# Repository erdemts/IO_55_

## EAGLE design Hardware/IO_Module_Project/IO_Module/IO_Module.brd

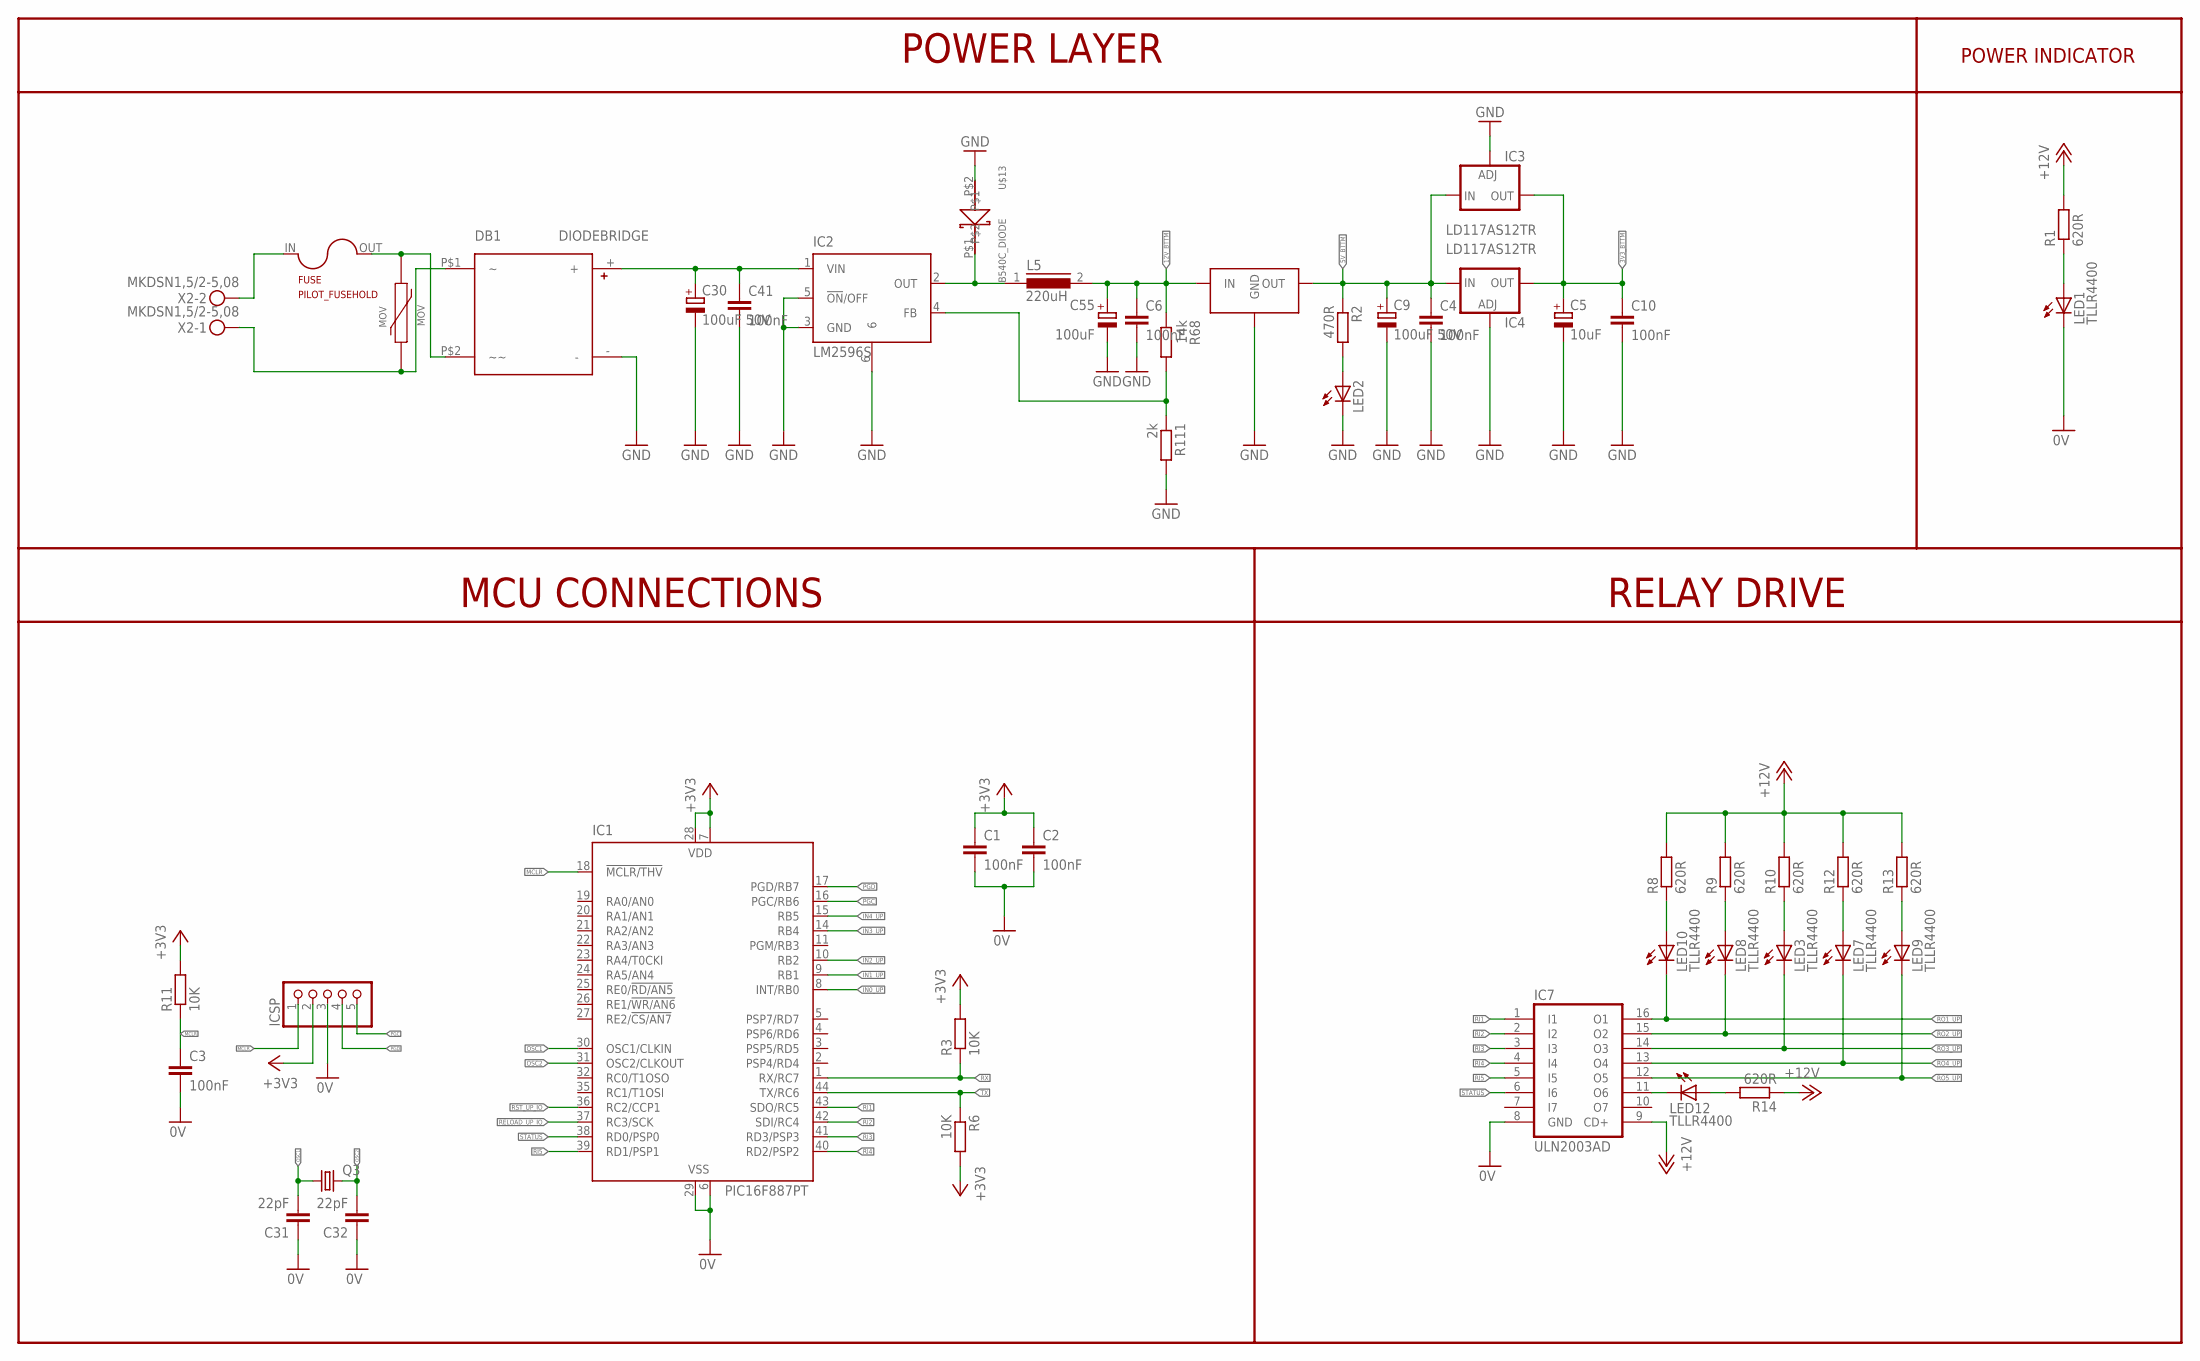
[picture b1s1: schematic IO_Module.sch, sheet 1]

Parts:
C1, C2, C3: 100nF; C0603K
C4, C6, C10, C41: 100nF; C0603
C5: 10uF; 153CLV-0505
C9, C30: 100uF 50V; 153CLV-0810
C31, C32: 22pF; C0805
C55: 100uF; 153CLV-0605
DB1: DIODEBRIDGE; SDIP
FUSE: PILOT_FUSEHOLD; RTM_FUSEHOLD
IC1: PIC16F887PT; TQFP44
IC2: LM2596S; TO263-5
IC3, IC4: LD117AS12TR; SOT223
IC7: ULN2003AD; SO16
ICSP: PINHD-1X5; 1X05
L5: 220uH; DR125
LED1, LED3, LED7, LED8, LED9, LED10, LED12: TLLR4400; LED3MM
LED2: LEDCHIPLED_0805; CHIPLED_0805
MOV: MOV-10D201K
Q3: CRYSTALHC49UP; HC49UP
R1, R8, R9, R10, R12, R13, R14: 620R; R0805
R2: 470R; R0805
R3, R6, R11: 10K; R0805
R68: 14k; M0805
R111: 2k; M0805
U$6: L7805CD2T-TR; VREG-7805-DPAK2
U$13: B540C_DIODE; SMC
X2: MKDSN1,5/2-5,08

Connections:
0V: C1.2, C2.2, C3.2, C31.1, C32.1, IC1.6 (VSS), IC1.29 (VSS), IC7.8 (GND), ICSP.3, LED1.K (C); also elsewhere on the board
3V3_BTTM: C5.+, C10.1, IC3.4 (OUT), IC4.4 (OUT); also elsewhere on the board
5V_BTTM: C4.1, C9.+, IC3.3 (IN), IC4.3 (IN), R2.1, U$6.VOUT (OUT)
12V_BTTM: C6.1, C55.+, L5.2, R68.1, U$6.VIN (IN); also elsewhere on the board
36V: C30.+, C41.1, DB1.+, IC2.1 (VIN)
+3V3: C1.1, C2.1, IC1.7 (VDD), IC1.28 (VDD), ICSP.2, R3.2, R6.2, R11.2; also elsewhere on the board
+12V: IC7.9 (CD+), R1.2, R8.2, R9.2, R10.2, R12.2, R13.2, R14.1; also elsewhere on the board
GND: C4.2, C5.-, C6.2, C9.-, C10.2, C30.-, C41.2, C55.-, DB1.-, IC2.3 (GND), IC2.5 (!ON!/OFF), IC2.6, IC3.1 (ADJ), IC4.1 (ADJ), LED2.C, R111.2, U$6.GND, U$13.P$2; also elsewhere on the board
IN0_UP: IC1.8 (INT/RB0); also elsewhere on the board
IN1_UP: IC1.9 (RB1); also elsewhere on the board
IN2_UP: IC1.10 (RB2); also elsewhere on the board
IN3_UP: IC1.14 (RB4); also elsewhere on the board
IN4_UP: IC1.15 (RB5); also elsewhere on the board
MCLR: C3.1, IC1.18 (!MCLR/THV), ICSP.1, R11.1
unnamed: LED2.A, R2.2
unnamed: DB1.P$2 (~~), FUSE.OUT, MOV.2
unnamed: DB1.P$1, MOV.1, X2.1
unnamed: FUSE.IN, X2.2
unnamed: LED1.A, R1.1
unnamed: IC7.11 (O6), LED12.K (C)
unnamed: LED10.A, R8.1
unnamed: LED8.A, R9.1
unnamed: LED3.A, R10.1
unnamed: LED7.A, R12.1
unnamed: LED9.A, R13.1
unnamed: LED12.A, R14.2
unnamed: IC2.2 (OUT), L5.1, U$13.P$1
unnamed: IC2.4 (FB), R68.2, R111.1
OSC1: C31.2, IC1.30 (OSC1/CLKIN), Q3.1
OSC2: C32.2, IC1.31 (OSC2/CLKOUT), Q3.2
PGC: IC1.16 (PGC/RB6), ICSP.5
PGD: IC1.17 (PGD/RB7), ICSP.4
RELOAD_UP_IO: IC1.37 (RC3/SCK); also elsewhere on the board
RI1: IC1.43 (SDO/RC5), IC7.1 (I1)
RI2: IC1.42 (SDI/RC4), IC7.2 (I2)
RI3: IC1.41 (RD3/PSP3), IC7.3 (I3)
RI4: IC1.40 (RD2/PSP2), IC7.4 (I4)
RI5: IC1.39 (RD1/PSP1), IC7.5 (I5)
RO1_UP: IC7.16 (O1), LED10.K (C); also elsewhere on the board
RO2_UP: IC7.15 (O2), LED8.K (C); also elsewhere on the board
RO3_UP: IC7.14 (O3), LED3.K (C); also elsewhere on the board
RO4_UP: IC7.13 (O4), LED7.K (C); also elsewhere on the board
RO5_UP: IC7.12 (O5), LED9.K (C); also elsewhere on the board
RST_UP_IO: IC1.36 (RC2/CCP1); also elsewhere on the board
RX: IC1.1 (RX/RC7), R3.1; also elsewhere on the board
STATUS: IC1.38 (RD0/PSP0), IC7.6 (I6)
TX: IC1.44 (TX/RC6), R6.1; also elsewhere on the board

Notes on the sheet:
POWER LAYER
MCU CONNECTIONS
RELAY DRIVE
POWER INDICATOR

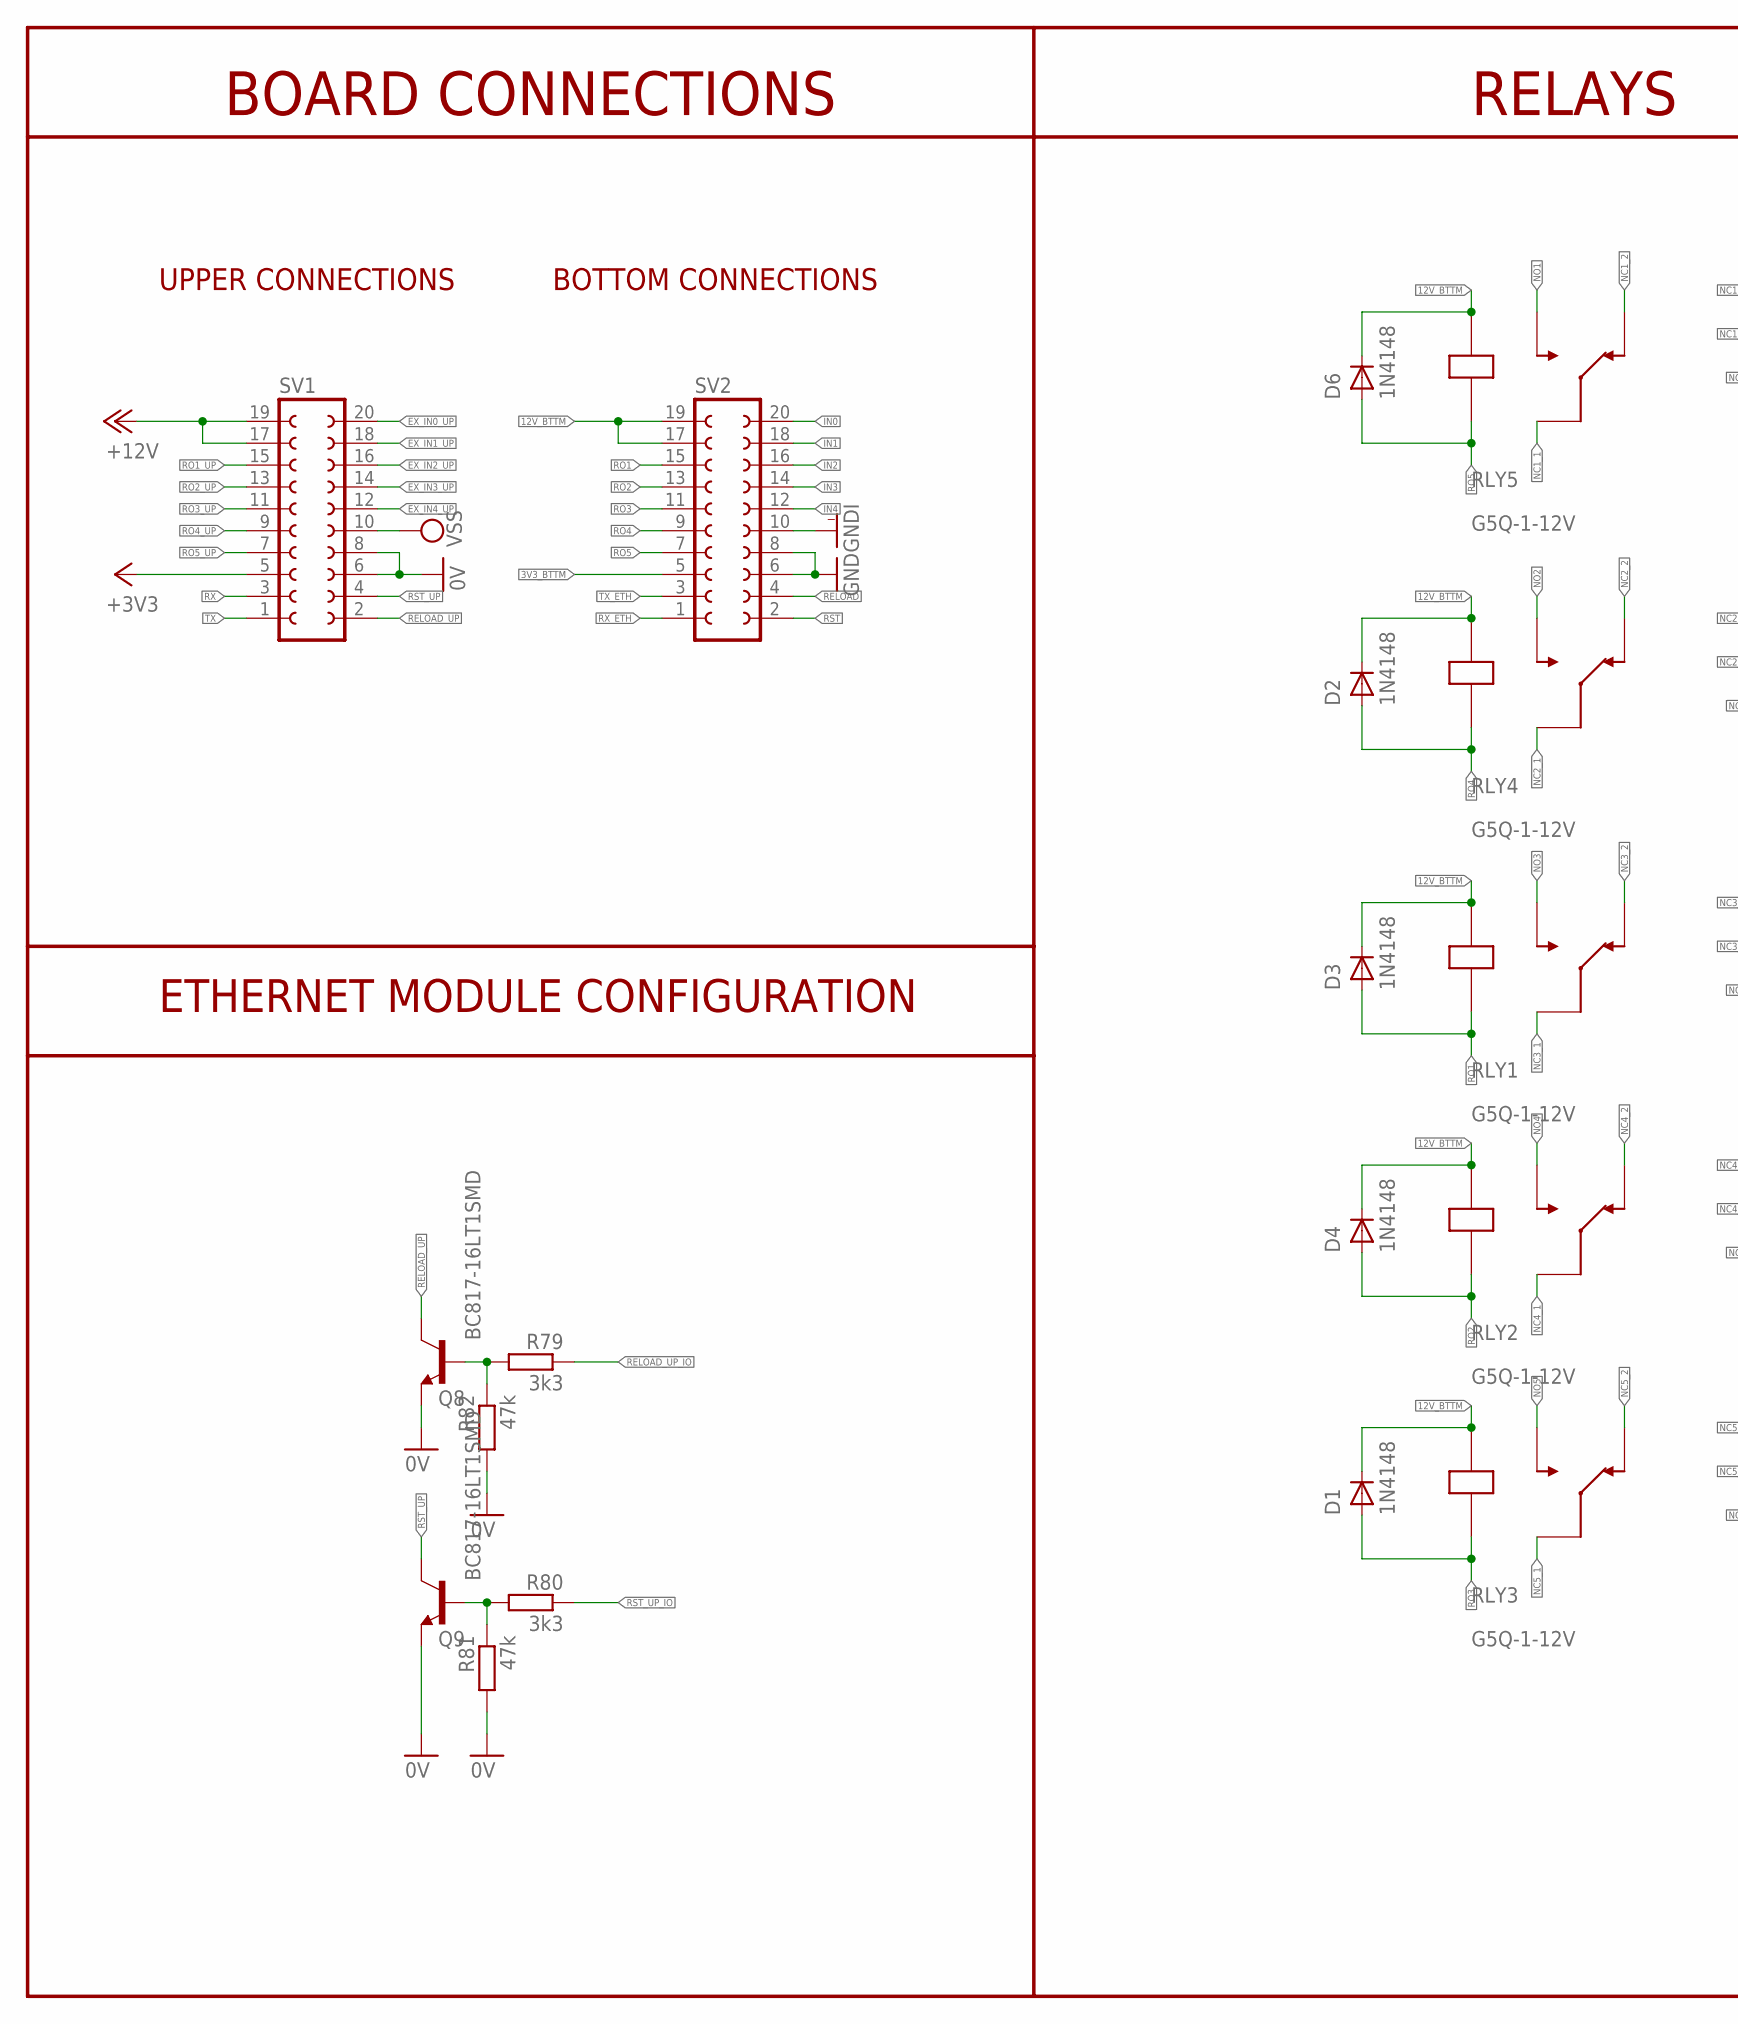
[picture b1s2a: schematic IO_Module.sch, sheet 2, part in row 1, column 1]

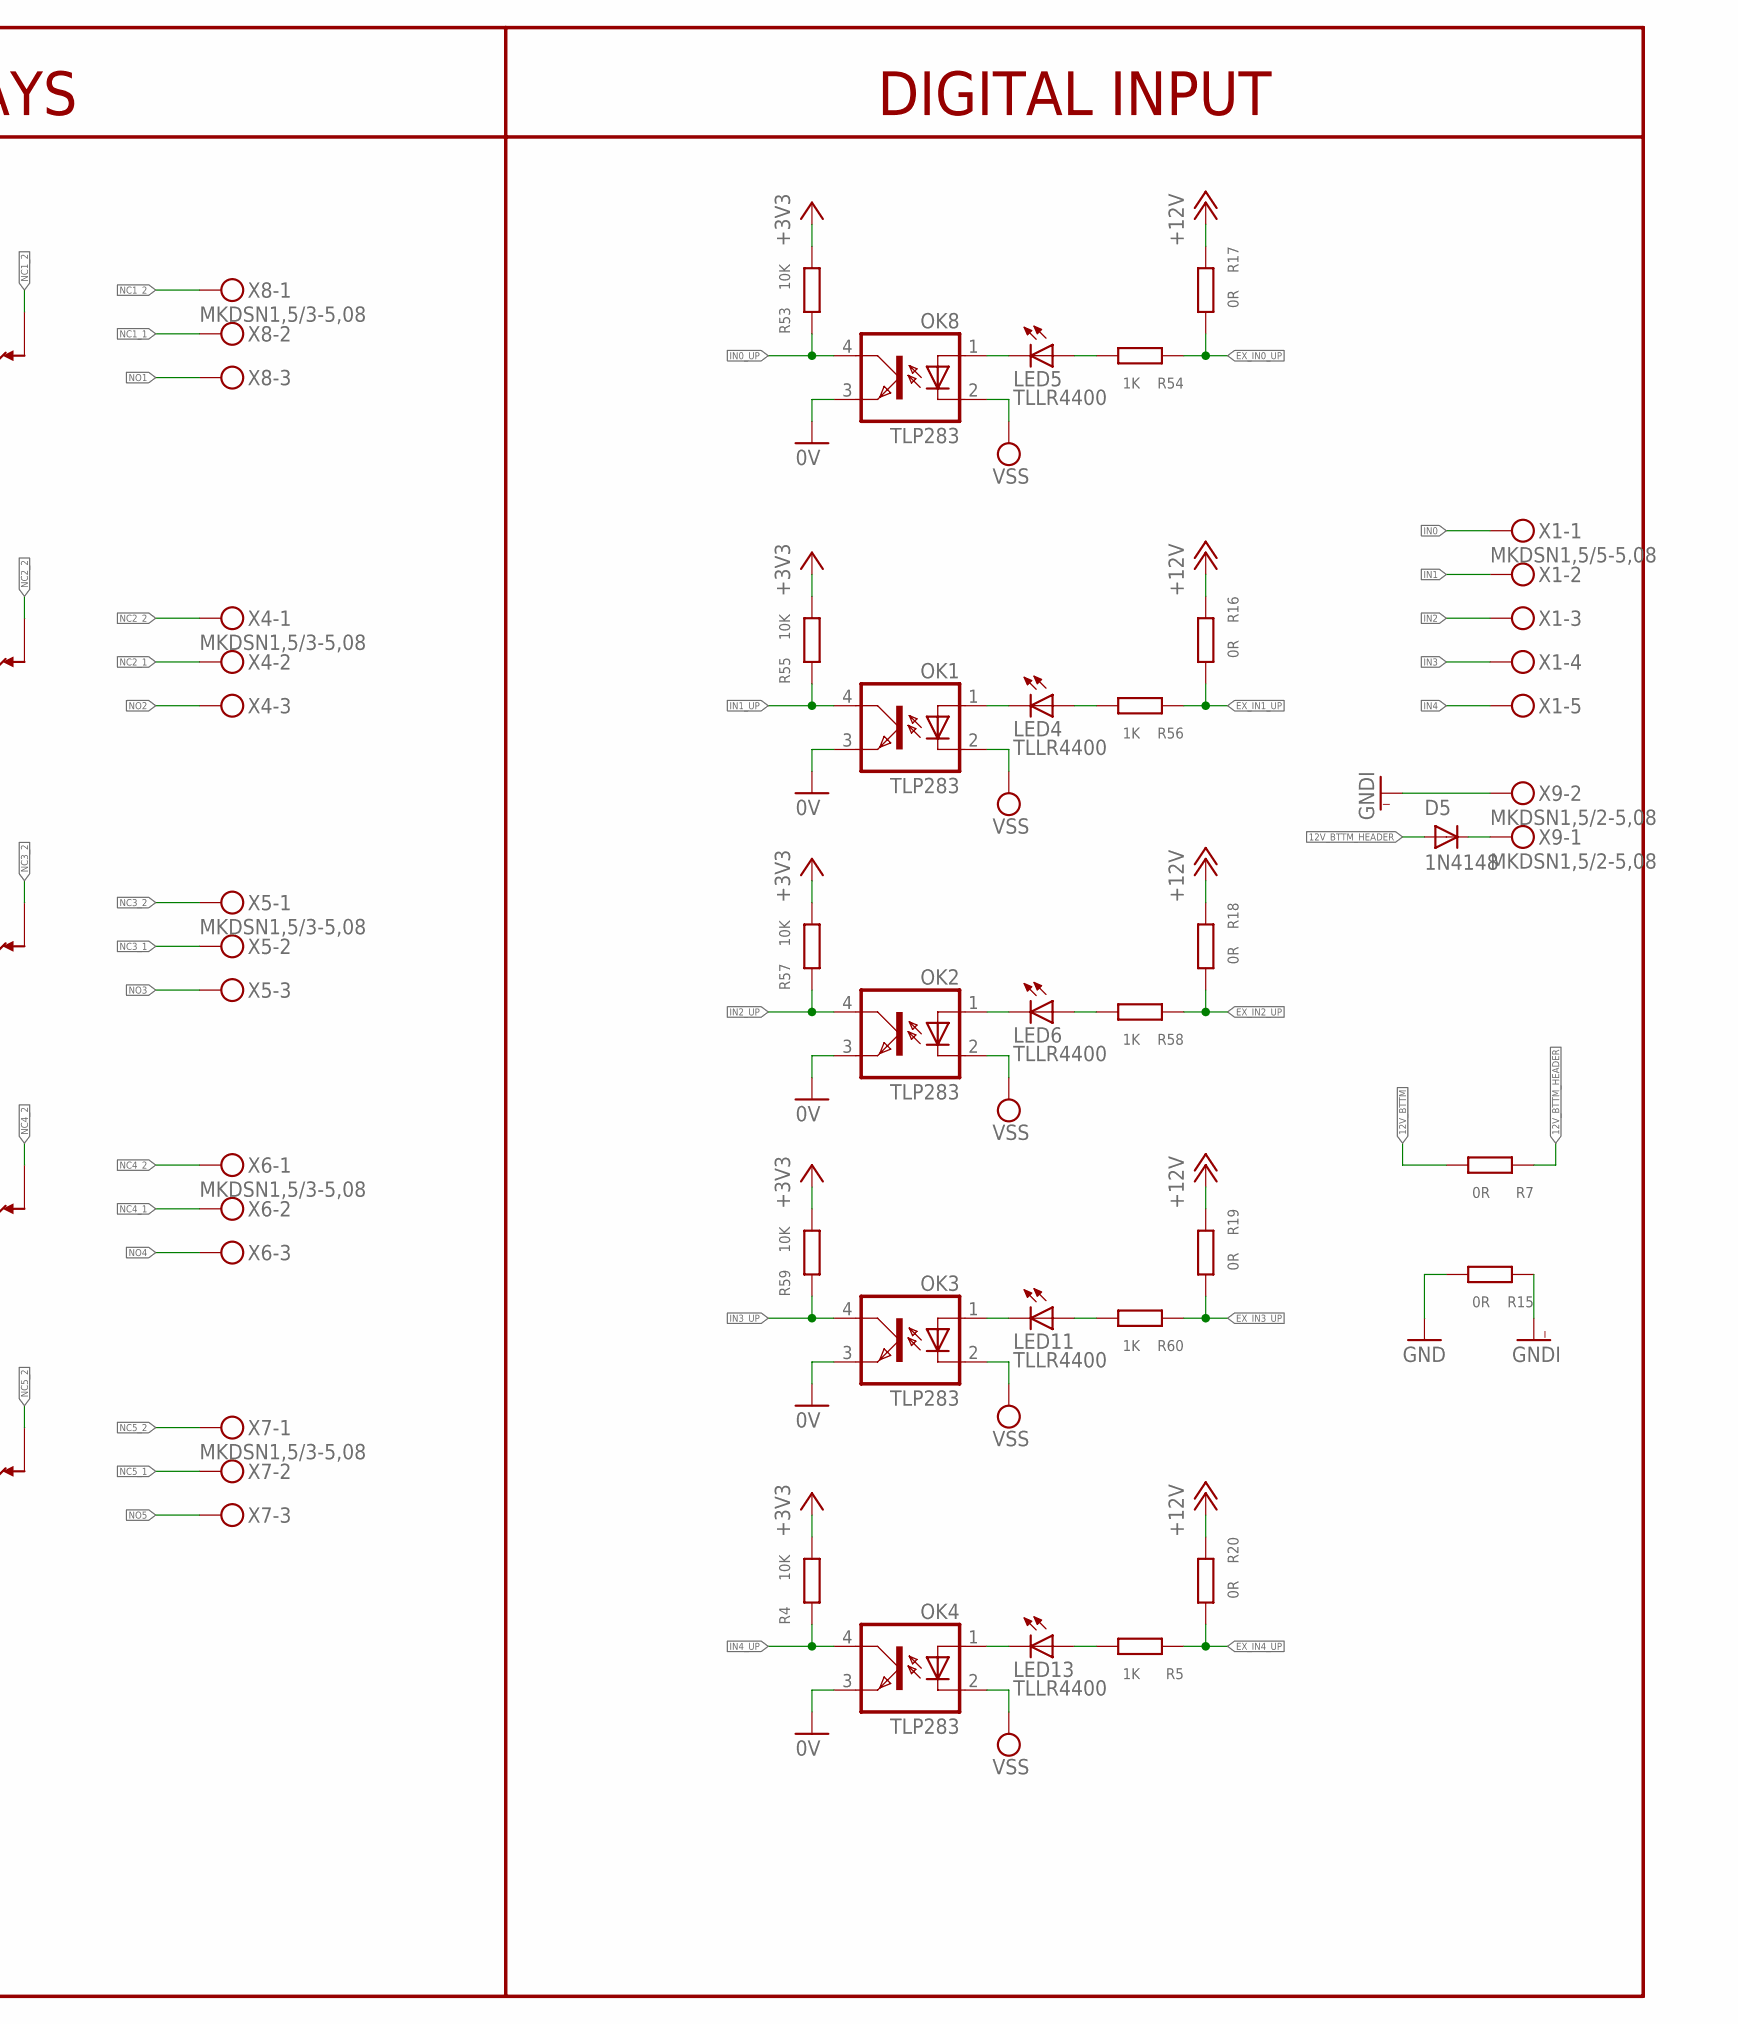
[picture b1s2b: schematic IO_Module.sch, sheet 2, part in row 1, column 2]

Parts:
D1, D2, D3, D4, D5, D6: 1N4148; SMA-DO214AC
LED4, LED5, LED6, LED11, LED13: TLLR4400; LED3MM
OK1, OK2, OK3, OK4, OK8: TLP283; MINI-FLAT-4
Q8, Q9: BC817-16LT1SMD; SOT23-BEC
R4, R53, R55, R57, R59: 10K; M0805
R5, R54, R56, R58, R60: 1K; M0805
R7, R15, R16, R17, R18, R19, R20: 0R; M0805
R79, R80: 3k3; R0805
R81, R82: 47k; R0805
RLY1, RLY2, RLY3, RLY4, RLY5: JW1FSN-DC12V; G5Q-1-12V
SV1, SV2: FE10-2
X1: MKDSN1,5/5-5,08
X4, X5, X6, X7, X8: MKDSN1,5/3-5,08
X9: MKDSN1,5/2-5,08

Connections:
0V: OK1.3 (EMIT), OK2.3 (EMIT), OK3.3 (EMIT), OK4.3 (EMIT), OK8.3 (EMIT), Q8.E, Q9.E, R81.2, R82.2, SV1.6, SV1.8; also elsewhere on the board
3V3_BTTM: SV2.5; also elsewhere on the board
12V_BTTM: D1.K (C), D2.K (C), D3.K (C), D4.K (C), D6.K (C), R7.2, RLY1.1, RLY2.1, RLY3.1, RLY4.1, RLY5.1, SV2.17, SV2.19; also elsewhere on the board
12V_BTTM_HEADER: D5.A, R7.1
+3V3: R4.2, R53.2, R55.2, R57.2, R59.2, SV1.5; also elsewhere on the board
+12V: R16.1, R17.1, R18.1, R19.1, R20.1, SV1.17, SV1.19; also elsewhere on the board
EX_IN0_UP: R17.2, R54.1, SV1.20
EX_IN1_UP: R16.2, R56.1, SV1.18
EX_IN2_UP: R18.2, R58.1, SV1.16
EX_IN3_UP: R19.2, R60.1, SV1.14
EX_IN4_UP: R5.1, R20.2, SV1.12
GND: R15.2, SV2.6, SV2.8; also elsewhere on the board
GNDI: R15.1, SV2.10, X9.2
IN0: SV2.20, X1.1
IN0_UP: OK8.4 (COL), R53.1; also elsewhere on the board
IN1: SV2.18, X1.2
IN1_UP: OK1.4 (COL), R55.1; also elsewhere on the board
IN2: SV2.16, X1.3
IN2_UP: OK2.4 (COL), R57.1; also elsewhere on the board
IN3: SV2.14, X1.4
IN3_UP: OK3.4 (COL), R59.1; also elsewhere on the board
IN4: SV2.12, X1.5
IN4_UP: OK4.4 (COL), R4.1; also elsewhere on the board
unnamed: LED13.K (C), OK4.1 (A)
unnamed: LED13.A, R5.2
unnamed: D5.K (C), X9.1
unnamed: LED5.K (C), OK8.1 (A)
unnamed: LED5.A, R54.2
unnamed: LED4.K (C), OK1.1 (A)
unnamed: LED4.A, R56.2
unnamed: LED6.K (C), OK2.1 (A)
unnamed: LED6.A, R58.2
unnamed: LED11.K (C), OK3.1 (A)
unnamed: LED11.A, R60.2
NC1_1: RLY5.3, X8.2
NC1_2: RLY5.4, X8.1
NC2_1: RLY4.3, X4.2
NC2_2: RLY4.4, X4.1
NC3_1: RLY1.3, X5.2
NC3_2: RLY1.4, X5.1
NC4_1: RLY2.3, X6.2
NC4_2: RLY2.4, X6.1
NC5_1: RLY3.3, X7.2
NC5_2: RLY3.4, X7.1
NO1: RLY5.5, X8.3
NO2: RLY4.5, X4.3
NO3: RLY1.5, X5.3
NO4: RLY2.5, X6.3
NO5: RLY3.5, X7.3
RELOAD: SV2.4; also elsewhere on the board
RELOAD_UP: Q8.C, SV1.2
RELOAD_UP_IO: R79.1; also elsewhere on the board
RO1: D3.A, RLY1.2, SV2.15
RO1_UP: SV1.15; also elsewhere on the board
RO2: D4.A, RLY2.2, SV2.13
RO2_UP: SV1.13; also elsewhere on the board
RO3: D1.A, RLY3.2, SV2.11
RO3_UP: SV1.11; also elsewhere on the board
RO4: D2.A, RLY4.2, SV2.9
RO4_UP: SV1.9; also elsewhere on the board
RO5: D6.A, RLY5.2, SV2.7
RO5_UP: SV1.7; also elsewhere on the board
RST: SV2.2; also elsewhere on the board
RST_UP: Q9.C, SV1.4
RST_UP_IO: R80.1; also elsewhere on the board
RX: SV1.3; also elsewhere on the board
RX_ETH: SV2.1; also elsewhere on the board
TX: SV1.1; also elsewhere on the board
TXD2: Q8.B, R79.2, R82.1
TXD3: Q9.B, R80.2, R81.1
TX_ETH: SV2.3; also elsewhere on the board
VSS: OK1.2 (C), OK2.2 (C), OK3.2 (C), OK4.2 (C), OK8.2 (C), SV1.10

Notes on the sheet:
UPPER CONNECTIONS
BOTTOM CONNECTIONS
ETHERNET MODULE CONFIGURATION
BOARD CONNECTIONS
RELAYS
DIGITAL INPUT

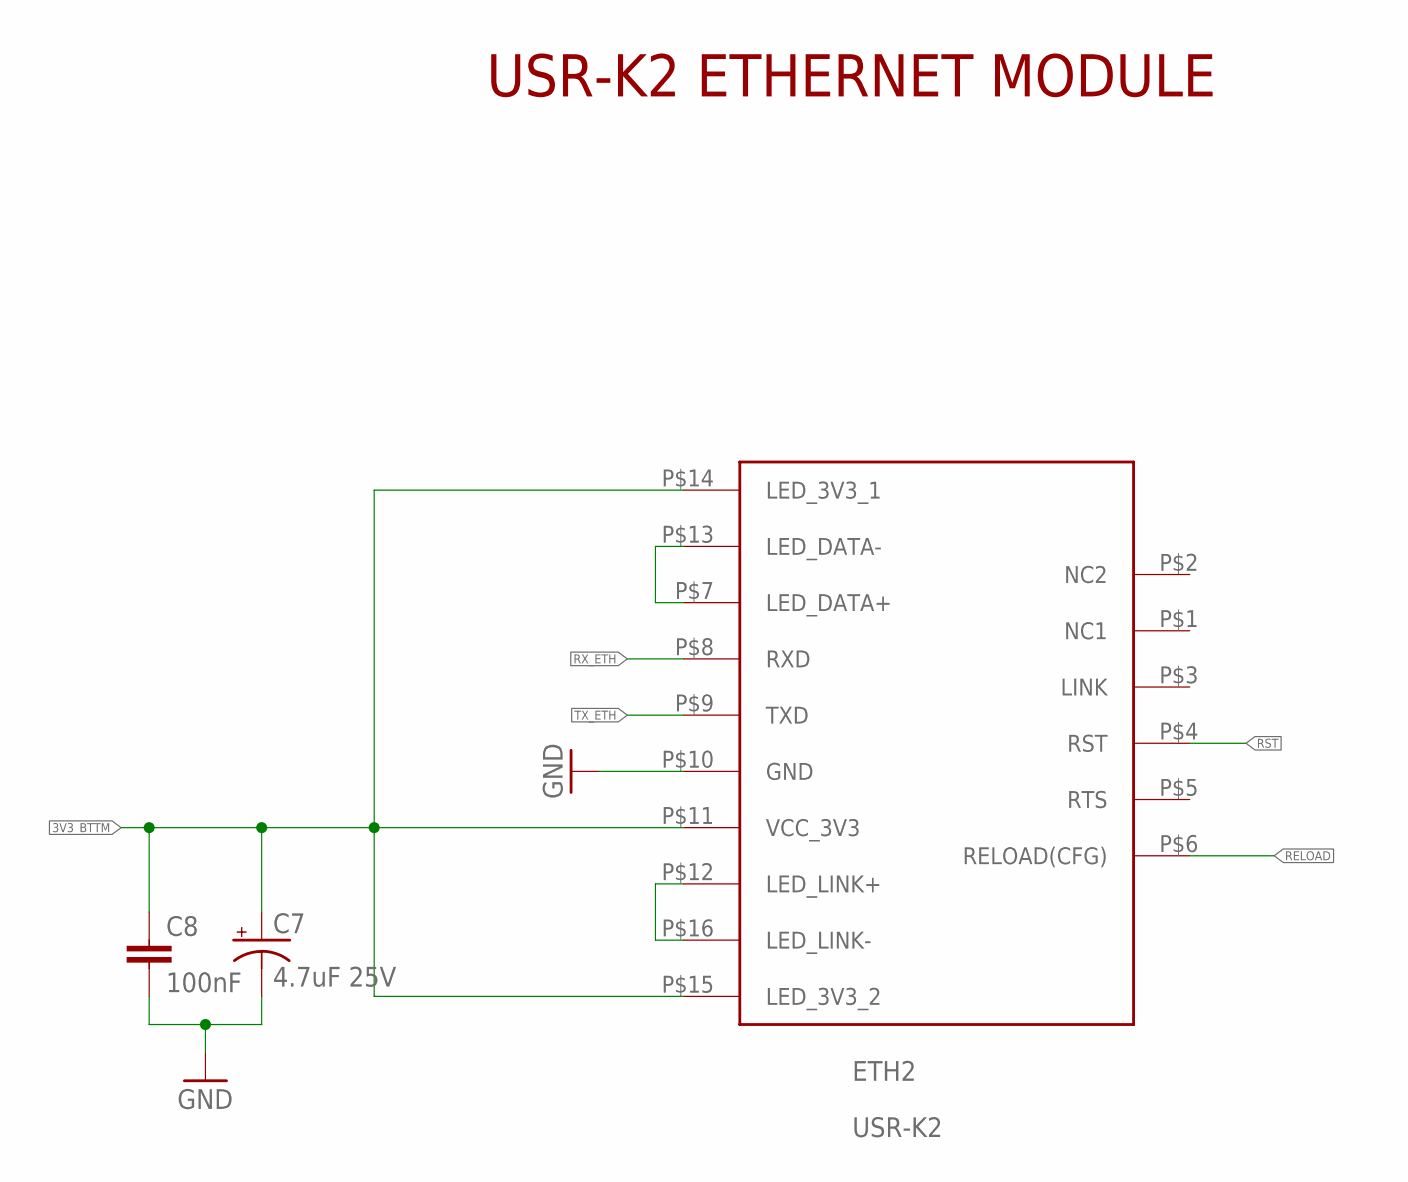
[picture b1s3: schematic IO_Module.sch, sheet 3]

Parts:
C7: 4.7uF 25V; A/3216-18R
C8: 100nF; C0603
ETH2: USR-K2

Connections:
3V3_BTTM: C7.+, C8.1, ETH2.P$11 (VCC_3V3), ETH2.P$14 (LED_3V3_1), ETH2.P$15 (LED_3V3_2); also elsewhere on the board
GND: C7.-, C8.2, ETH2.P$10 (GND); also elsewhere on the board
unnamed: ETH2.P$12 (LED_LINK+), ETH2.P$16 (LED_LINK-)
unnamed: ETH2.P$7 (LED_DATA+), ETH2.P$13 (LED_DATA-)
RELOAD: ETH2.P$6 (RELOAD(CFG)); also elsewhere on the board
RST: ETH2.P$4 (RST); also elsewhere on the board
RX_ETH: ETH2.P$8 (RXD); also elsewhere on the board
TX_ETH: ETH2.P$9 (TXD); also elsewhere on the board

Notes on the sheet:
USR-K2 ETHERNET MODULE

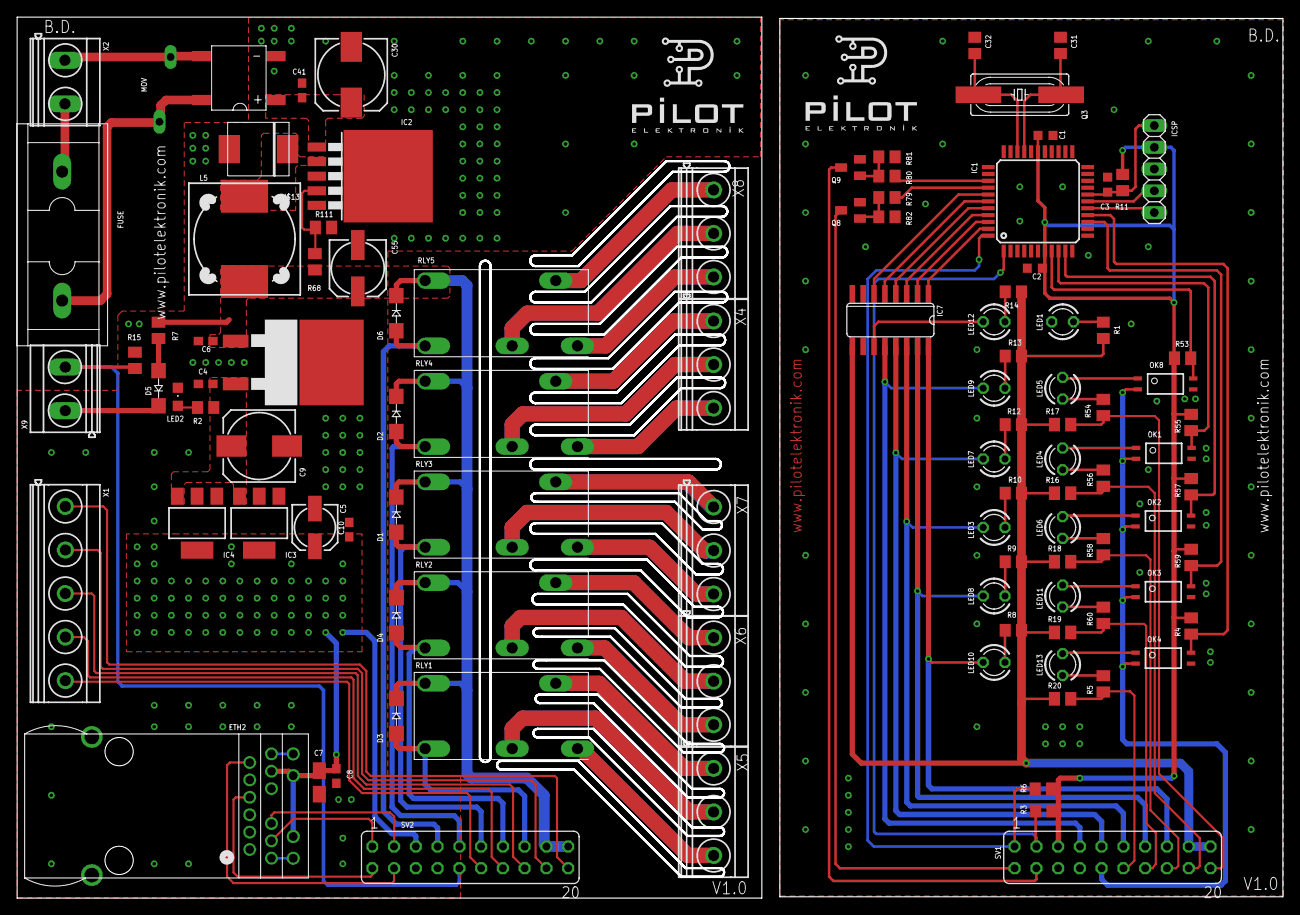
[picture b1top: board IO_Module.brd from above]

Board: 2 copper layers, 147.4 x 102.5 mm, 104 parts (0 on the bottom side), 101 nets.

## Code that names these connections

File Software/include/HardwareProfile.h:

/*******************************************************************************
 *
 * FileName     : HardwareProfile.h ( BusIdDongle Hardware profile file )
 * Dependencies :
 * Description  :
 * Processor    : PIC16F887
 * Compiler     : Hi-tech Picc 9.83
 * Linker       :
 * Company      : Inno Technology Incorporated
 *
 * Software License Agreement
 * Copyright (C) 2011 - 2012 Inno Technology Inc.  All rights
 * reserved.
 *
 * Version    Author                     Date             Comment
 *~~~~~~~~~~~~~~~~~~~~~~~~~~~~~~~~~~~~~~~~~~~~~~~~~~~~~~~~~~~~~~~~~~~~~~~~~~~~~~
 * 1.0        Erdem Tayfun Salman       11/14/2014       Initial Version
 ******************************************************************************/
#ifndef HARDWAREPROFILE_H
#define HARDWAREPROFILE_H

#include <htc.h>

#define _XTAL_FREQ	8000000


/*****************************************************************************
 *	Uart
 *****************************************************************************/
#define UARTTX_TRIS                 (TRISCbits.TRISC6)
#define UARTRX_TRIS                 (TRISCbits.TRISC7)

#define ETH_RESET_TRIS              (TRISCbits.TRISC3)
#define ETH_RESET                   (PORTCbits.RC3)

#define ETH_RELOAD_TRIS             (TRISCbits.TRISC2)
#define ETH_RELOAD                  (PORTCbits.RC2)


/*****************************************************************************
 *	Relays
 *****************************************************************************/
#define RELAY_5_TRIS            (TRISCbits.TRISC5)//RELAY_1
#define RELAY_5                 (PORTCbits.RC5)

#define RELAY_4_TRIS            (TRISCbits.TRISC4)
#define RELAY_4                 (PORTCbits.RC4)

#define RELAY_3_TRIS            (TRISDbits.TRISD3)
#define RELAY_3                 (PORTDbits.RD3)

#define RELAY_2_TRIS            (TRISDbits.TRISD2)
#define RELAY_2                 (PORTDbits.RD2)

#define RELAY_1_TRIS            (TRISDbits.TRISD1)
#define RELAY_1                 (PORTDbits.RD1)



/*****************************************************************************
 *	INPUT PINS
 *****************************************************************************/

#define INPUT_1_TRIS            (TRISBbits.TRISB0)
#define INPUT_1                 (PORTBbits.RB0)

#define INPUT_2_TRIS            (TRISBbits.TRISB1)
#define INPUT_2                 (PORTBbits.RB1)

#define INPUT_3_TRIS            (TRISBbits.TRISB2)
#define INPUT_3                 (PORTBbits.RB2)

#define INPUT_4_TRIS            (TRISBbits.TRISB4)
#define INPUT_4                 (PORTBbits.RB4)

#define INPUT_5_TRIS            (TRISBbits.TRISB5)
#define INPUT_5                 (PORTBbits.RB5)

/*****************************************************************************
 *	I/O Pins
 *****************************************************************************/
#define LED_BLUE                 (PORTDbits.RD0) //RED LED
#define LED_BLUE_TRIS		     (TRISDbits.TRISD0) //RED LED






#endif

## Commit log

2018-06-07 Yeni haberleşme protokolü eklendi. IO fonksiyonları düzenlendi.
